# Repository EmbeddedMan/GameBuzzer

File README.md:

# GameBuzzer
Book club game buzzer project using LoRa Feathers

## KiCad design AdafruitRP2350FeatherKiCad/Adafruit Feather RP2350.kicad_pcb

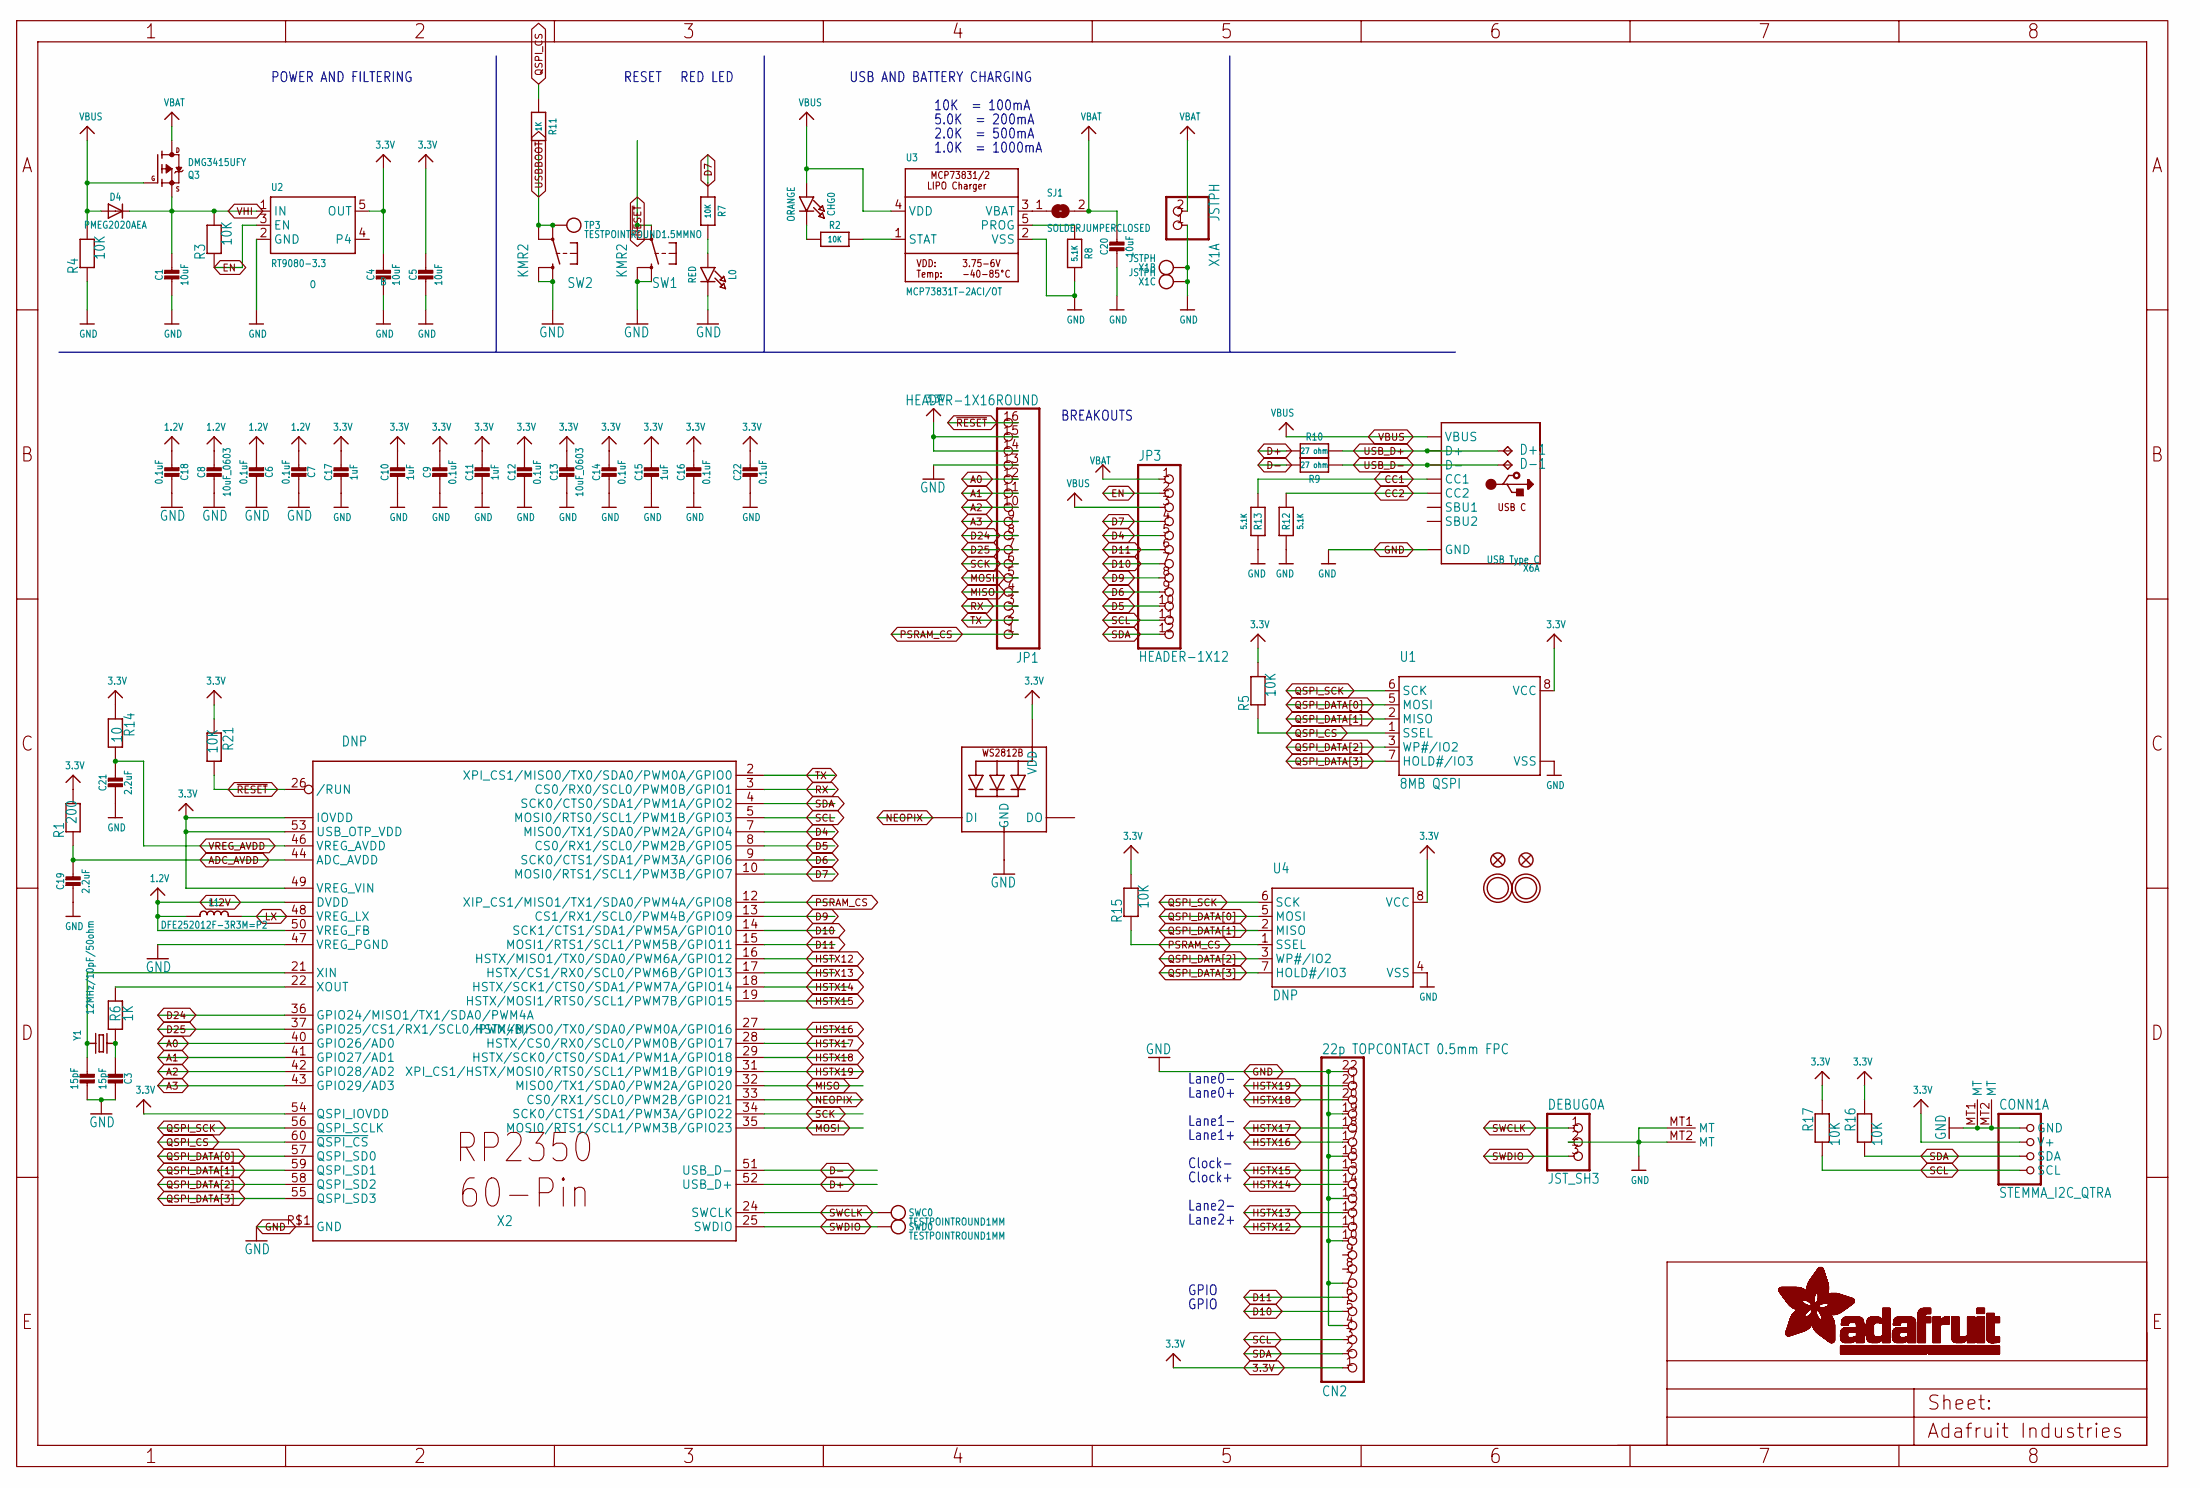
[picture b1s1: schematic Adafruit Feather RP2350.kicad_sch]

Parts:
C1, C4, C20: 10uF; 0805-NO
C2, C3: 15pF; _0402NO
C5: 10uF; 0603-NO
C6, C7, C9, C12, C14, C16, C18, C22: 0.1uF; _0402NO
C8, C13: 10uF_0603; _0603MP
C10, C11, C15, C17: 1uF; _0402NO
C19, C21: 2.2uF; _0402NO
CHG0: ORANGE; CHIPLED_0603_NOOUTLINE
CN2: 22p TOPCONTACT 0.5mm FPC; FPC_22PIN
CONN1: STEMMA_I2C_QTRA; JST_SH4_RA; LCSC C145961
D4: PMEG2020AEA; SOD-323F
D+1: TPB1,27; B1,27
D-1: TPB1,27; B1,27
DEBUG0: JST_SH3; JST_SH3_RA
JP1: HEADER-1X16ROUND; 1X16_ROUND
JP3: HEADER-1X12; 1X12_ROUND
L0: RED; CHIPLED_0603_NOOUTLINE
L1: DFE252012F-3R3M=P2; INDUCTOR_1007
LED1: WS2812B_SK6805_1515; SK6805_1515; LCSC C2890035
Q3: DMG3415UFY; DFN2015-3
R1: 200; _0402NO
R2, R3, R4, R5, R7, R15, R16, R17, R21: 10K; _0402NO
R6, R11: 1K; _0402NO
R8, R12, R13: 5.1K; _0402NO
R9, R10: 27 ohm; _0402NO
R14: 10; _0402NO
SJ1: SOLDERJUMPERCLOSED; SOLDERJUMPER_CLOSEDWIRE
SW1, SW2: KMR2; BTN_RKB2_4.6X2.8
SWC0: TESTPOINTROUND1MM; TESTPOINT_ROUND_1MM
SWD0: TESTPOINTROUND1MM; TESTPOINT_ROUND_1MM
TP3: TESTPOINTROUND1.5MMNO; TESTPOINT_ROUND_1.5MM_NO
U1: 8MB QSPI; USON8_4X4
U2: RT9080-3.3; SOT23-5; JLC_ROTATION 0
U3: MCP73831T-2ACI/OT; SOT23-5; JLC_ROTATION 0
U4: DNP; SOIC8_150MIL
U$31, U$32: MOUNTINGHOLE2.5; MOUNTINGHOLE_2.5_PLATED
U$34, U$35: FIDUCIAL_1MM
X1: JSTPH; JSTPH2_BATT; LCSC C47647
X2: DNP; QFN60_7MM_REDUCEDEPAD
X6: USB Type C; USB_C_CUSB31-CFM2AX-01-X; LCSC C165948
Y1: 12MHz/10pF/50ohm; CRYSTAL_2.5X2

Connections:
1.2V: C6.2, C7.2, C8.1, C18.2, L1.P$1 (1), X2.6 (DVDD), X2.23 (DVDD), X2.39 (DVDD), X2.50 (VREG_FB)
3.3V: C4.1, C5.1, C9.1, C10.1, C11.1, C12.1, C13.1, C14.1, C15.1, C16.1, C17.1, C22.1, CN2.1, CONN1.2 (V+), JP1.14, JP1.15, LED1.2 (VDD), R1.2, R5.2, R14.1, R15.2, R16.1, R17.1, R21.1, U1.8 (VCC), U2.5 (OUT), U4.8 (VCC), X2.1 (IOVDD), X2.11 (IOVDD), X2.20 (IOVDD), X2.30 (IOVDD), X2.38 (IOVDD), X2.45 (IOVDD), X2.49 (VREG_VIN), X2.53 (USB_OTP_VDD), X2.54 (QSPI_IOVDD)
A0: JP1.12, X2.40 (GPIO26/AD0)
A1: JP1.11, X2.41 (GPIO27/AD1)
A2: JP1.10, X2.42 (GPIO28/AD2)
A3: JP1.9, X2.43 (GPIO29/AD3)
ADC_AVDD: C19.1, R1.1, X2.44 (ADC_AVDD)
CC1: R13.2, X6.A5 (CC1)
CC2: R12.2, X6.B5 (CC2)
D4: JP3.5, X2.7 (MISO0/TX1/SDA0/PWM2A/GPIO4)
D5: JP3.10, X2.8 (CS0/RX1/SCL0/PWM2B/GPIO5)
D6: JP3.9, X2.9 (SCK0/CTS1/SDA1/PWM3A/GPIO6)
D7: JP3.4, R7.1, X2.10 (MOSI0/RTS1/SCL1/PWM3B/GPIO7)
D9: JP3.8, X2.13 (CS1/RX1/SCL0/PWM4B/GPIO9)
D10: CN2.5, JP3.7, X2.14 (SCK1/CTS1/SDA1/PWM5A/GPIO10)
D11: CN2.6, JP3.6, X2.15 (MOSI1/RTS1/SCL1/PWM5B/GPIO11)
D24: JP1.8, X2.36 (GPIO24/MISO1/TX1/SDA0/PWM4A)
D25: JP1.7, X2.37 (GPIO25/CS1/RX1/SCL0/PWM4B/)
D+: R10.2, X2.52 (USB_D+)
D-: R9.2, X2.51 (USB_D-)
EN: JP3.2, R3.1, U2.3 (EN)
GND: C1.2, C2.1, C3.1, C4.2, C5.2, C6.1, C7.1, C8.2, C9.2, C10.2, C11.2, C12.2, C13.2, C14.2, C15.2, C16.2, C17.2, C18.1, C19.2, C20.2, C21.2, C22.2, CN2.4, CN2.7, CN2.10, CN2.13, CN2.16, CN2.19, CN2.22, CONN1.1 (GND), CONN1.MT1 (MT), CONN1.MT2 (MT), DEBUG0.2, DEBUG0.MT1 (MT), DEBUG0.MT2 (MT), JP1.13, L0.C, LED1.4 (GND), R4.1, R8.2, R12.1, R13.1, SW1.B (S), SW1.B' (S1), SW2.B (S), SW2.B' (S1), U1.4 (VSS), U1.PAD (VSS), U2.2 (GND), U3.2 (VSS), U4.4 (VSS), X1.1, X1.NC1, X1.NC2, X2.47 (VREG_PGND), X2.P$1 (GND), X6.A1B12 (GND), X6.B1A12 (GND)
HSTX12: CN2.11, X2.16 (HSTX/MISO1/TX0/SDA0/PWM6A/GPIO12)
HSTX13: CN2.12, X2.17 (HSTX/CS1/RX0/SCL0/PWM6B/GPIO13)
HSTX14: CN2.14, X2.18 (HSTX/SCK1/CTS0/SDA1/PWM7A/GPIO14)
HSTX15: CN2.15, X2.19 (HSTX/MOSI1/RTS0/SCL1/PWM7B/GPIO15)
HSTX16: CN2.17, X2.27 (HSTX/MISO0/TX0/SDA0/PWM0A/GPIO16)
HSTX17: CN2.18, X2.28 (HSTX/CS0/RX0/SCL0/PWM0B/GPIO17)
HSTX18: CN2.20, X2.29 (HSTX/SCK0/CTS0/SDA1/PWM1A/GPIO18)
HSTX19: CN2.21, X2.31 (XPI_CS1/HSTX/MOSI0/RTS0/SCL1/PWM1B/GPIO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)
LX: L1.P$2 (2), X2.48 (VREG_LX)
MISO: JP1.4, X2.32 (MISO0/TX1/SDA0/PWM2A/GPIO20)
MOSI: JP1.5, X2.35 (MOSI0/RTS1/SCL1/PWM3B/GPIO23)
unnamed: CHG0.C, R2.1
unnamed: L0.A, R7.2
unnamed: R2.2, U3.1 (STAT)
unnamed: R8.1, U3.5 (PROG)
unnamed: C2.2, X2.21 (XIN), Y1.3 (2)
unnamed: C3.2, R6.1, Y1.1
unnamed: R6.2, X2.22 (XOUT)
unnamed: SJ1.1, U3.3 (VBAT)
NEOPIX: LED1.1 (DI), X2.33 (CS0/RX1/SCL0/PWM2B/GPIO21)
PSRAM_CS: JP1.1, R15.1, U4.1 (SSEL), X2.12 (XIP_CS1/MISO1/TX1/SDA0/PWM4A/GPIO8)
QSPI_CS: R5.1, R11.1, U1.1 (SSEL), X2.60 (~QSPI_CS)
QSPI_DATA[0]: U1.5 (MOSI), U4.5 (MOSI), X2.57 (QSPI_SD0)
QSPI_DATA[1]: U1.2 (MISO), U4.2 (MISO), X2.59 (QSPI_SD1)
QSPI_DATA[2]: U1.3 (WP#/IO2), U4.3 (WP#/IO2), X2.58 (QSPI_SD2)
QSPI_DATA[3]: U1.7 (HOLD#/IO3), U4.7 (HOLD#/IO3), X2.55 (QSPI_SD3)
QSPI_SCK: U1.6 (SCK), U4.6 (SCK), X2.56 (QSPI_SCLK)
RX: JP1.3, X2.3 (CS0/RX0/SCL0/PWM0B/GPIO1)
SCK: JP1.6, X2.34 (SCK0/CTS1/SDA1/PWM3A/GPIO22)
SCL: CN2.3, CONN1.4 (SCL), JP3.11, R17.2, X2.5 (MOSI0/RTS0/SCL1/PWM1B/GPIO3)
SDA: CN2.2, CONN1.3 (SDA), JP3.12, R16.2, X2.4 (SCK0/CTS0/SDA1/PWM1A/GPIO2)
SWCLK: DEBUG0.1, SWC0.P$1, X2.24 (SWCLK)
SWDIO: DEBUG0.3, SWD0.P$1, X2.25 (SWDIO)
TX: JP1.2, X2.2 (XPI_CS1/MISO0/TX0/SDA0/PWM0A/GPIO0)
USBBOOT: R11.2, SW2.A, SW2.A' (P1), TP3.P$1
USB_D+: D+1.TP, R10.1, X6.A6 (D+), X6.B6 (D+)
USB_D-: D-1.TP, R9.1, X6.A7 (D-), X6.B7 (D-)
VBAT: C20.1, JP3.1, Q3.3 (D), SJ1.2, X1.2
VBUS: CHG0.A, D4.A, JP3.3, Q3.1 (G), R4.2, U3.4 (VDD), X6.A4B9 (VBUS), X6.B4A9 (VBUS)
VHI: C1.1, D4.C, Q3.2 (S), R3.2, U2.1 (IN)
VREG_AVDD: C21.1, R14.2, X2.46 (VREG_AVDD)
~RESET: JP1.16, R21.2, SW1.A, SW1.A' (P1), X2.26 (/RUN)

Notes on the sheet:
RED LED
10K = 100mA
Lane0+
GPIO
Lane2+
Lane0-
1.0K = 1000mA
USB AND BATTERY CHARGING
Lane1-
Lane2-
Clock-
RESET
POWER AND FILTERING
2.0K = 500mA
Lane1+
BREAKOUTS
Clock+
5.0K = 200mA

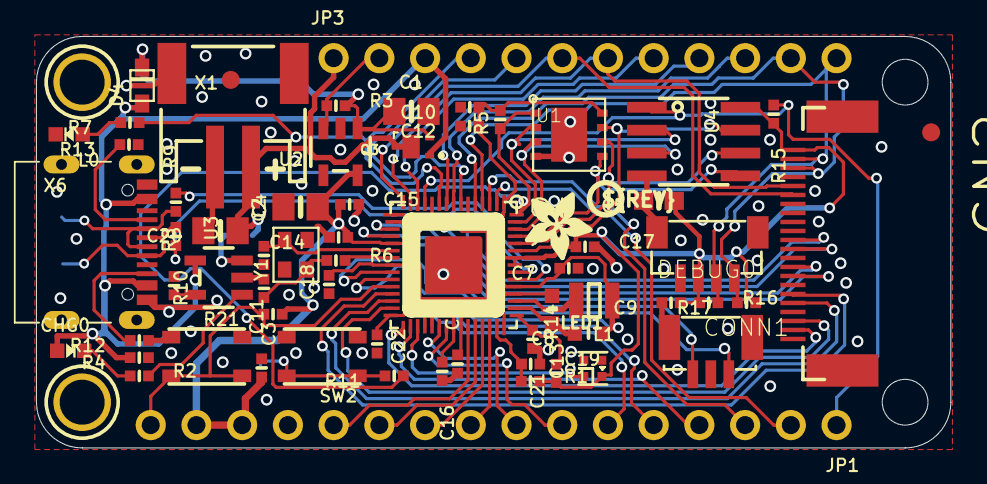
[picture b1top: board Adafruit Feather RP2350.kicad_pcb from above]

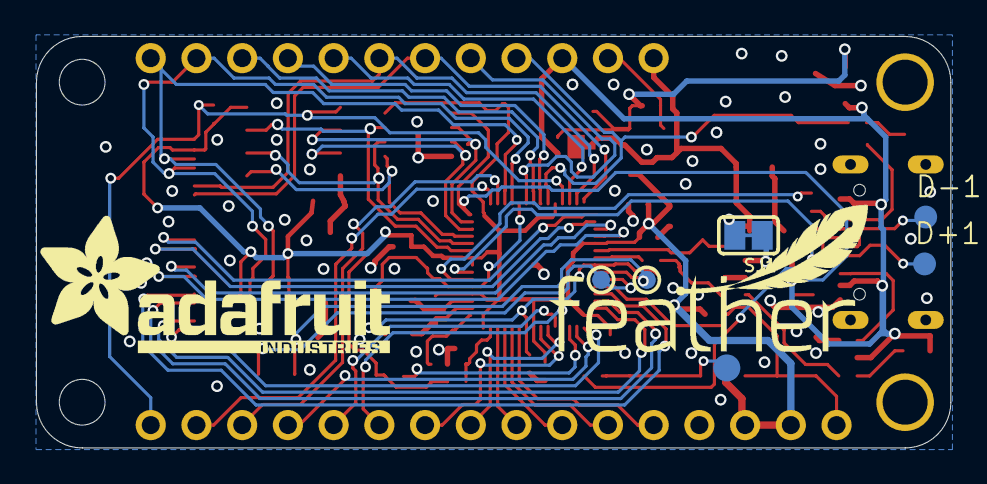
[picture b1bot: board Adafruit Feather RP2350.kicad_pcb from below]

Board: 2 copper layers, 50.8 x 22.9 mm, 145 parts (39 on the bottom side), 64 nets.

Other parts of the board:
PLABEL0: PLABEL0
PLABEL1: PLABEL1
PLABEL2: PLABEL2
PLABEL3: PLABEL3
PLABEL4: PLABEL4
PLABEL5: PLABEL5
PLABEL6: PLABEL6
PLABEL7: PLABEL7
PLABEL8: PLABEL8
PLABEL9: PLABEL9
PLABEL10: PLABEL10
PLABEL11: PLABEL11
PLABEL12: PLABEL12
PLABEL13: PLABEL13
PLABEL14: PLABEL14
PLABEL15: PLABEL15
PLABEL16: PLABEL16
PLABEL17: PLABEL17
PLABEL18: PLABEL18
PLABEL19: PLABEL19
PLABEL20: PLABEL20
PLABEL21: PLABEL21
PLABEL22: PLABEL22
PLABEL23: PLABEL23
PLABEL24: PLABEL24
PLABEL25: PLABEL25
PLABEL26: PLABEL26
PLABEL27: PLABEL27
PLABEL28: PLABEL28
PLABEL29: PLABEL29
PLABEL30: PLABEL30
PLABEL31: PLABEL31
PLABEL32: PLABEL32
PLABEL33: PLABEL33
PLABEL34: PLABEL34
PLABEL35: PLABEL35
PLABEL36: PLABEL36
PLABEL37: PLABEL37
PLABEL38: PLABEL38
PLABEL39: PLABEL39
PLABEL40: PLABEL40
PLABEL41: PLABEL41
PLABEL42: PLABEL42
PLABEL43: PLABEL43
PLABEL44: PLABEL44
PLABEL45: PLABEL45
PLABEL46: PLABEL46
PLABEL47: PLABEL47
PLABEL48: PLABEL48
PLABEL49: PLABEL49
PLABEL50: PLABEL50
PLABEL51: PLABEL51
PLABEL52: PLABEL52
PLABEL53: PLABEL53
PLABEL54: PLABEL54
PLABEL55: PLABEL55
PLABEL56: PLABEL56
PLABEL57: PLABEL57
PLABEL58: PLABEL58
PLABEL59: PLABEL59
PLABEL60: PLABEL60
PLABEL61: PLABEL61
PLABEL62: PLABEL62
PLABEL63: PLABEL63
PLABEL64: PLABEL64
PLABEL65: PLABEL65
PLABEL67: PLABEL67
PLABEL68: PLABEL68
U$73: ADAFRUIT_3.5MM
U$74: PCBFEAT-REV-040
U$75: FEATHERLOGO_MED
U$76: ADAFRUIT_TEXT_20MM
UNK_HOLE_0: dummyfp0
UNK_HOLE_1: dummyfp1

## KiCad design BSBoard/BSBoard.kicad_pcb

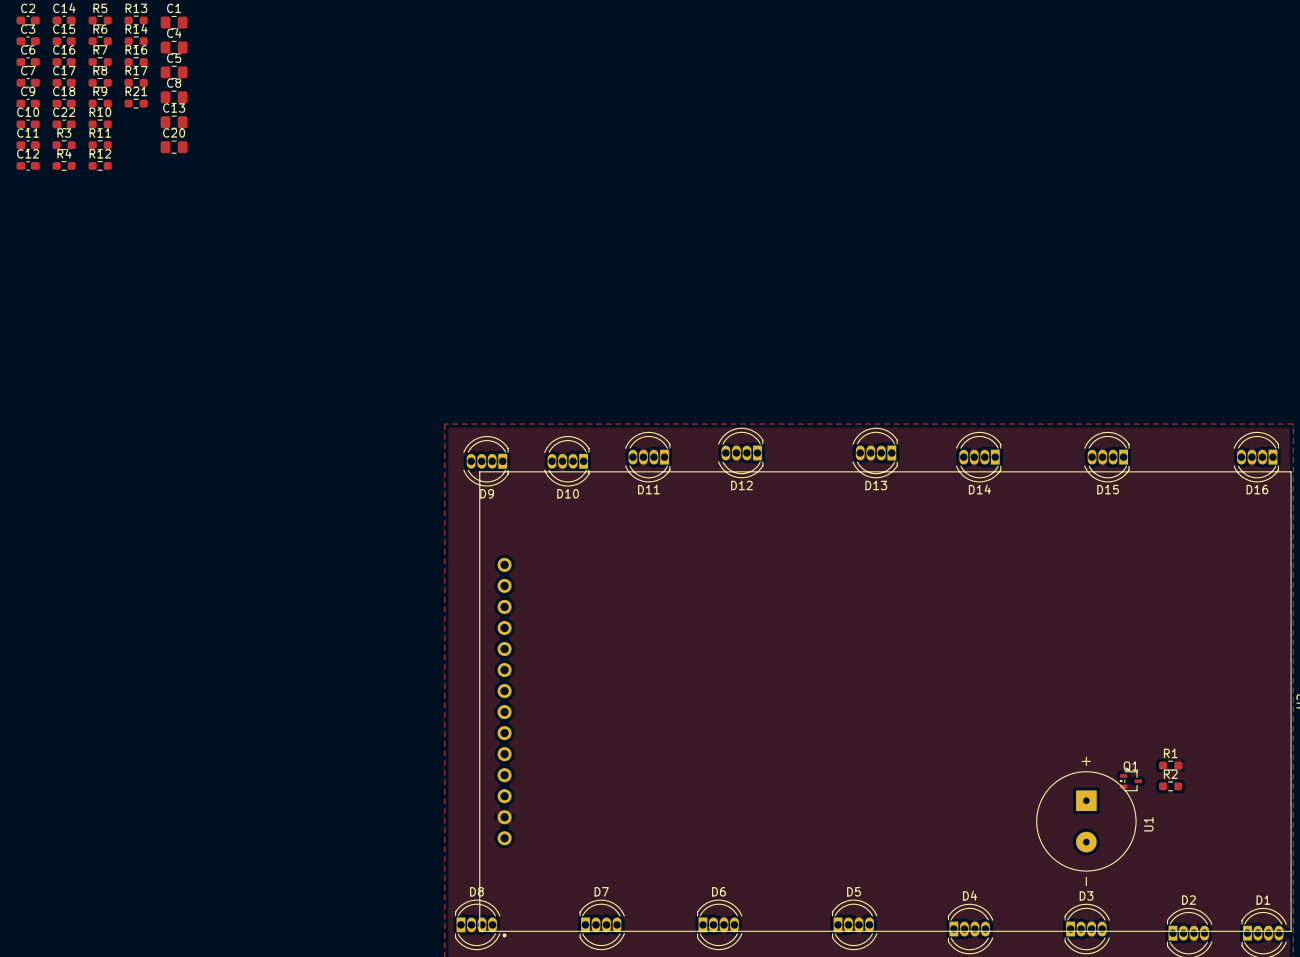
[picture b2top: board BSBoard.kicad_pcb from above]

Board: 2 copper layers, 56 parts (0 on the bottom side), 24 nets, no tracks yet.

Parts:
C1, C4, C5, C8, C13, C20: 10uF; C_0805_2012Metric_Pad1.18x1.45mm_HandSolder
C2, C3: 15pF; C_0603_1608Metric_Pad1.08x0.95mm_HandSolder
C6, C7, C9, C12, C14, C16, C18, C22: 0.1uF; C_0603_1608Metric_Pad1.08x0.95mm_HandSolder
C10, C11, C15, C17: 1uF; C_0603_1608Metric_Pad1.08x0.95mm_HandSolder
D1, D2, D3, D4, D5, D6, D7, D8, D9, D10, D11, D12, D13, D14, D15, D16: NeoPixel_THT; LED_D5.0mm-4_RGB
Q1: DMG1012T; SOT-323_SC-70
R1, R4, R5, R7, R8, R10, R21: 10K; R_0603_1608Metric_Pad0.98x0.95mm_HandSolder
R2: 220; R_0603_1608Metric_Pad0.98x0.95mm_HandSolder
R3: 200; R_0603_1608Metric_Pad0.98x0.95mm_HandSolder
R6, R11: 1K; R_0603_1608Metric_Pad0.98x0.95mm_HandSolder
R9, R12, R13: 5.1K; R_0603_1608Metric_Pad0.98x0.95mm_HandSolder
R14: 10; R_0603_1608Metric_Pad0.98x0.95mm_HandSolder
R16, R17: 27 ohm; R_0603_1608Metric_Pad0.98x0.95mm_HandSolder
U1: CMT-1209-590T; XDCR_CMT-1209-590T
U2: MSP3526; MSP3526_3.5in_LCD_Module_14Pin_P2.54mm

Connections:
1.2V: C6.2, C7.2, C8.1, C18.2
3.3V: C4.1, C5.1, C9.1, C10.1, C11.1, C12.1, C13.1, C14.1, C15.1, C16.1, C17.1, C22.1, R3.2, R10.2, R14.1, R21.1
+3V3: D1.2 (VDD), D2.2 (VDD), D3.2 (VDD), D4.2 (VDD), D5.2 (VDD), D6.2 (VDD), D7.2 (VDD), D8.2 (VDD), D9.2 (VDD), D10.2 (VDD), D11.2 (VDD), D12.2 (VDD), D13.2 (VDD), D14.2 (VDD), D15.2 (VDD), D16.2 (VDD), U1.P, U2.1 (VCC), U2.8 (LED)
GND: C1.2, C2.1, C3.1, C4.2, C5.2, C6.1, C7.1, C8.2, C9.2, C10.2, C11.2, C12.2, C13.2, C14.2, C15.2, C16.2, C17.2, C18.1, C20.2, C22.2, D1.3 (GND), D2.3 (GND), D3.3 (GND), D4.3 (GND), D5.3 (GND), D6.3 (GND), D10.3 (GND), D11.3 (GND), D12.3 (GND), D13.3 (GND), D14.3 (GND), D15.3 (GND), D16.3 (GND), Q1.2 (S), R1.2, R4.1, R9.2, R12.1, R13.1, U2.2 (GND)
unnamed: C3.2, R6.1
unnamed: D1.1 (DOUT), D2.4 (DIN)
unnamed: D2.1 (DOUT), D3.4 (DIN)
unnamed: D3.1 (DOUT), D4.4 (DIN)
unnamed: D4.1 (DOUT), D5.4 (DIN)
unnamed: D5.1 (DOUT), D6.4 (DIN)
unnamed: D6.1 (DOUT), D7.4 (DIN)
unnamed: D7.1 (DOUT), D8.4 (DIN)
unnamed: D8.1 (DOUT), D9.4 (DIN)
unnamed: D9.1 (DOUT), D10.4 (DIN)
unnamed: D10.1 (DOUT), D11.4 (DIN)
unnamed: D11.1 (DOUT), D12.4 (DIN)
unnamed: D12.1 (DOUT), D13.4 (DIN)
unnamed: D13.1 (DOUT), D14.4 (DIN)
unnamed: D14.1 (DOUT), D15.4 (DIN)
unnamed: D15.1 (DOUT), D16.4 (DIN)
unnamed: Q1.3 (D), U1.N
unnamed: Q1.1 (G), R1.1, R2.2
QSPI_CS: R10.1, R11.1
VHI: C1.1, R5.2

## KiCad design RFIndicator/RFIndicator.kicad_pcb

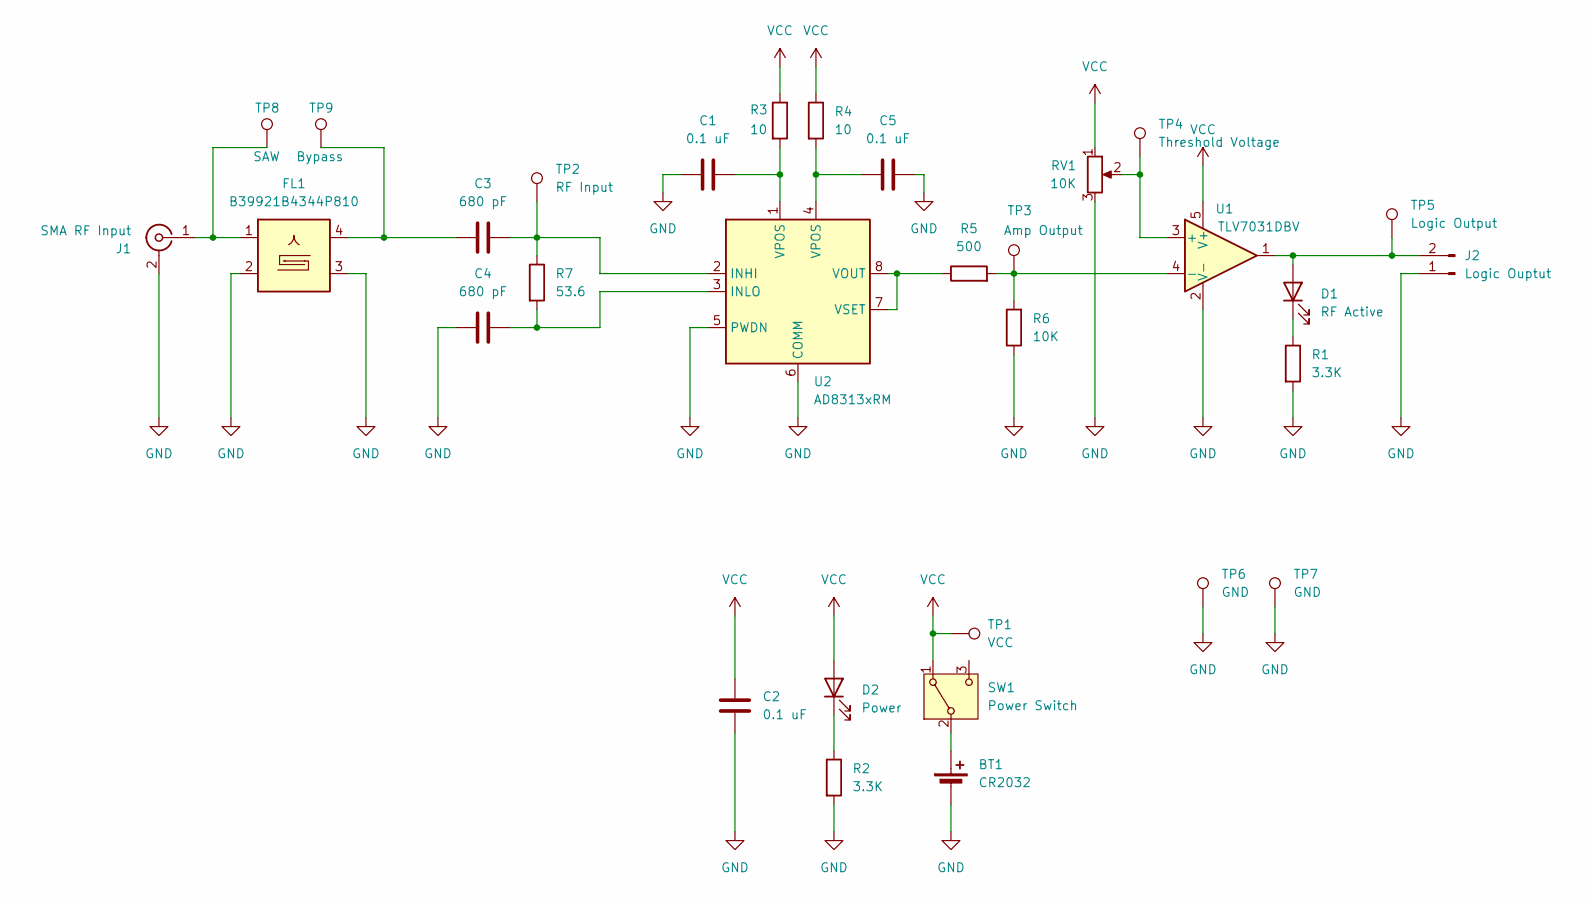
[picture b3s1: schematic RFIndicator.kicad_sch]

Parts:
BT1: CR2032; BatteryHolder_MYOUNG_BS-07-A1BJ001_CR2032
C1, C2, C5: 0.1 uF; C_0603_1608Metric_Pad1.08x0.95mm_HandSolder
C3, C4: 680 pF; C_0603_1608Metric_Pad1.08x0.95mm_HandSolder
D1: RF Active; LED_0603_1608Metric
D2: Power; LED_0603_1608Metric
FL1: B39921B4344P810; Filter_1411-5_1.4x1.1mm
J1: SMA RF Input; SMA_Samtec_SMA-J-P-H-ST-EM1_EdgeMount
J2: Logic Ouptut; PinHeader_1x02_P2.54mm_Vertical
R1, R2: 3.3K; R_0603_1608Metric_Pad0.98x0.95mm_HandSolder
R3, R4: 10; R_0603_1608Metric_Pad0.98x0.95mm_HandSolder
R5: 500; R_0603_1608Metric_Pad0.98x0.95mm_HandSolder
R6: 10K; R_0603_1608Metric_Pad0.98x0.95mm_HandSolder
R7: 53.6; R_0603_1608Metric_Pad0.98x0.95mm_HandSolder
RV1: 10K; Potentiometer_Bourns_3266W_Vertical
SW1: Power Switch; SW_SPDT_CK_JS102011SAQN
TP1: VCC; TestPoint_Loop_D2.54mm_Drill1.5mm_Beaded
TP2: RF Input; TestPoint_Loop_D2.54mm_Drill1.5mm_Beaded
TP3: Amp Output; TestPoint_Loop_D2.54mm_Drill1.5mm_Beaded
TP4: Threshold Voltage; TestPoint_Loop_D2.54mm_Drill1.5mm_Beaded
TP5: Logic Output; TestPoint_Loop_D2.54mm_Drill1.5mm_Beaded
TP6, TP7: GND; TestPoint_Loop_D2.54mm_Drill1.5mm_Beaded
TP8: SAW; TestPoint_Pad_1.0x1.0mm
TP9: Bypass; TestPoint_Pad_1.0x1.0mm
U1: TLV7031DBV; SOT-23-5
U2: AD8313xRM; MSOP-8_3x3mm_P0.65mm

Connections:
GND: BT1.2 (-), C1.1, C2.2, C4.1, C5.2, FL1.2, FL1.3, FL1.5, J1.2 (Ext), J2.1, R1.2, R2.2, R6.1, RV1.3, TP6.1, TP7.1, U1.2 (V-), U2.5 (PWDN), U2.6 (COMM)
unnamed: BT1.1 (+), SW1.2 (B)
unnamed: C1.2, R3.2, U2.1 (VPOS)
unnamed: C3.1, FL1.4, TP9.1
unnamed: C5.1, R4.2, U2.4 (VPOS)
unnamed: D1.2 (A), J2.2, TP5.1, U1.1
unnamed: D1.1 (K), R1.1
unnamed: D2.1 (K), R2.1
unnamed: FL1.1, J1.1 (In), TP8.1
unnamed: RV1.2, TP4.1, U1.3 (+)
unnamed: R5.2, R6.2, TP3.1, U1.4 (-)
unnamed: C3.2, R7.1, TP2.1, U2.2 (INHI)
unnamed: C4.2, R7.2, U2.3 (INLO)
unnamed: R5.1, U2.7 (VSET), U2.8 (VOUT)
VCC: C2.1, D2.2 (A), R3.1, R4.1, RV1.1, SW1.1 (A), TP1.1, U1.5 (V+)

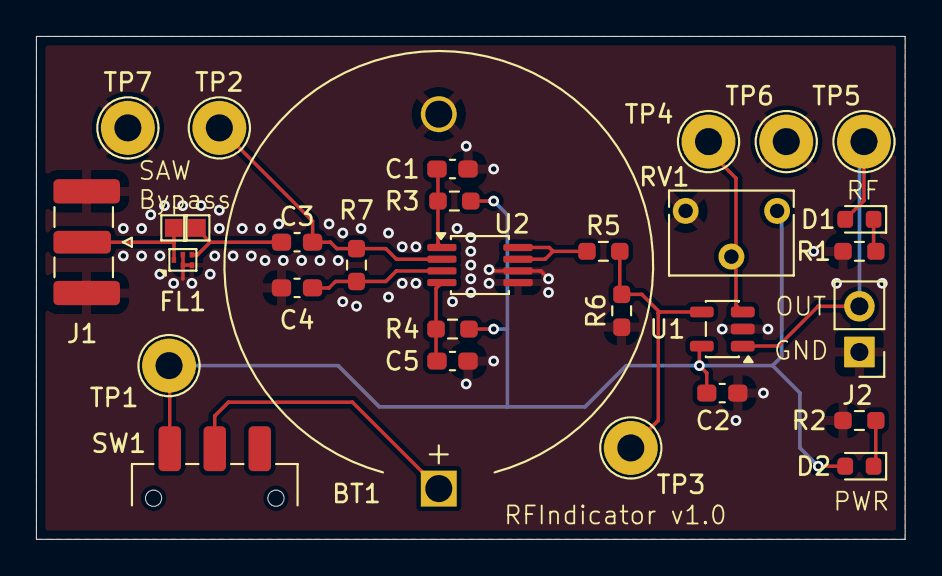
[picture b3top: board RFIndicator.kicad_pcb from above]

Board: 2 copper layers, 48.3 x 27.9 mm, 31 parts (0 on the bottom side), 15 nets.

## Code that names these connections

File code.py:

# SPDX-FileCopyrightText: 2023 Kattni Rembor for Adafruit Industries
# SPDX-License-Identifier: MIT

"""
CircuitPython Feather RP2040 RFM95 Packet Receive Demo

This demo waits for a "button" packet. When the first packet is received, the NeoPixel LED
lights up red. The next packet changes it to green. The next packet changes it to blue.
Subsequent button packets cycle through the same colors in the same order.

This example is meant to be paired with the Packet Send Demo code running
on a second Feather RP2040 RFM95 board.

board.A0 (GPIO26)
board.A1 (GPIO27)
board.A2 (GPIO28)
board.A3 (GPIO29)
board.BOOT board.BUTTON board.D7 (GPIO7)
board.D0 board.RX (GPIO1)
board.D1 board.TX (GPIO0)
board.D10 (GPIO10)
board.D11 (GPIO11)
board.D12 (GPIO12)
board.D13 board.LED (GPIO13)
board.D24 (GPIO24)
board.D25 (GPIO25)
board.D4 board.NEOPIXEL (GPIO4)
board.D5 (GPIO5)
board.D6 (GPIO6)
board.D9 (GPIO9)
board.MISO (GPIO8)
board.MOSI (GPIO15)
board.RFM_CS (GPIO16)
board.RFM_IO0 (GPIO21)
board.RFM_IO1 (GPIO22)
board.RFM_IO2 (GPIO23)
board.RFM_IO3 (GPIO19)
board.RFM_IO4 (GPIO20)
board.RFM_IO5 (GPIO18)
board.RFM_RST (GPIO17)
board.SCK (GPIO14)
board.SCL (GPIO3)
board.SDA (GPIO2)

"""

import board
import digitalio
import neopixel
import adafruit_rfm9x
import time

# LED setup (for heartbeat)
led = digitalio.DigitalInOut(board.LED)
led.direction = digitalio.Direction.OUTPUT

# Set up NeoPixel.
pixel = neopixel.NeoPixel(board.NEOPIXEL, 1)
pixel.brightness = 0.5

# Define the possible NeoPixel colors.
color_values = [
    (255, 0, 0),
    (0, 255, 0),
    (0, 0, 255),
]
COLOR_RED = 0
COLOR_GREEN = 1
COLOR_BLUE = 2

# Define radio frequency in MHz. Must match your
# module. Can be a value like 915.0, 433.0, etc.
RADIO_FREQ_MHZ = 915.0

# Define Chip Select and Reset pins for the radio module.
CS = digitalio.DigitalInOut(board.RFM_CS)
RESET = digitalio.DigitalInOut(board.RFM_RST)

# Initialise RFM95 radio
rfm95 = adafruit_rfm9x.RFM9x(board.SPI(), CS, RESET, RADIO_FREQ_MHZ)

# Set up the onboard button
btn = digitalio.DigitalInOut(board.BUTTON)
btn.direction = digitalio.Direction.INPUT
btn.pull = digitalio.Pull.UP

###################
#  BASE STATION   #
###################

# All packets sent between any nodes will consist of the folowing:
# Each packet will consist of four bytes.
# Packet Structure:
#   Byte 1: Source address (0 = base station, 1 - 8 = hand controllers)
#   Byte 2: Destination address (0 = base station, 1 - 8 = hand controllers)
#   Byte 3: Status byte
#   Byte 4: Battery voltage (0 = 0.0v, 255 = 4.7v)
#
# Status byte for hand controller -> base station
# 0 = Heartbeat only. Button not pushed.
# 1 = Button has been pushed.
#
# Status byte for base station -> hand controller (ACK packets)
# 0 = Turn your LED to green (system reset)
# 1 = Turn your LED to red (your button press has been recorded)
#
# Battery voltage byte will always be 0 in packets sent from base station.
# Heartbeats will be sent from hand controller to base station every 1s.
# When a hand controller button push happens, the hand controller will
#   immediately send a packet with status = 1 to the base station.
# When the hand controller button is released, a heartbeat packet is
#   immediately sent.
# Every packet received at the base station must be acknowledged by an ACK
#   packet.
# The ACK packet has the base station's address (0) as the first byte.
# The ACK packet has the destination hand controller's address (1-8) as the
#   second byte.
# The base station has a screen. This screen displays the current
#   state of every hand controller (pressed/unpressed/no comms) in real
#   time as well as the controller's battery level.
# The base station has a 'Reset' button. When this button is pressed,
#   the base station resets the display and begins watching for the first
#   button push from each hand controller and records the order in which
#   their buttons were pushed.
# When in the 'reset' state (waiting for first controller's button push)
#   the base station will ack with a status byte value of 0 which will make
#   all of the hand controler's neopixels green, indicating that the system
#   is waiting for the first person to press their button.
# Once the base station receives the first button push message from a
#   hand controller, it will begin acking that hand controller with a status
#   byte value of 1 which will make the hand controller's neopixel turn red,
#   indicating that the button push has been registered at the base station.
# After reset, the base station will display its neopixel as green. Once it
#   receives the first button press it will display as red.

# Define the two types of ack packets the base station will send to the hand controllers
ack_green_pkt = bytes([0, 0, 0, 0])
ack_red_pkt = bytes([0, 0, 1, 0])

# Keep track of what 'mode' we are in
base_station_is_reset = True

# Stores the time at which we reset and started waiting for button press packets
# And we start each boot being in reset mode
reset_start_time = time.monotonic()

# Stores the absolute time of reception of the first button push packet from
# each hand controller. 0.0 means the base station has not received a button
# push packet since the last reset.
button_push_time = [0.0, 0.0, 0.0, 0.0, 0.0, 0.0, 0.0, 0.0]


# Wait to receive packets.
print("Reset: waiting for hand controllers to press buttons")
# Start off with our LED showing green
pixel.fill(color_values[COLOR_GREEN])

while True:
    # Toggle the red LED on the board
    led.value = not led.value

    # Look for button press to reset our state
    if not btn.value:
        base_station_is_reset = True
        button_push_time = [0.0, 0.0, 0.0, 0.0, 0.0, 0.0, 0.0, 0.0]
        pixel.fill(color_values[COLOR_GREEN])
        print("System now reset")

    # Look for a new packet - wait up to 0.25 second:
    packet = rfm95.receive(timeout=0.25)
    # If no packet was received during the timeout then None is returned.
    if packet is not None:
        # Check the packet length
        if len(packet) == 4:
            hc_src_addr = int.from_bytes(packet[0:1], "big")
            hc_dst_addr = int.from_bytes(packet[1:2], "big")
            hc_status = int.from_bytes(packet[2:3], "big")
            hc_battery = int.from_bytes(packet[3:4], "big")
            if hc_src_addr != 0 and hc_src_addr <= 8:
                if hc_dst_addr == 0:
                    if hc_status == 0:  # heartbeat packet
                        if button_push_time[hc_src_addr] == 0.0:
                            rfm95.send(bytes([0, hc_src_addr, 0, 0]))
                        else:
                            rfm95.send(bytes([0, hc_src_addr, 1, 0]))
                    else:
                        if hc_status == 1:  # button push packet
                            if button_push_time[hc_src_addr] == 0.0:
                                print("Got button push from hand controller ", hc_src_addr)
                                button_push_time[hc_src_addr] = time.monotonic();
                            pixel.fill(color_values[COLOR_RED])
                            rfm95.send(bytes([0, hc_src_addr, 1, 0]))
                        else:
                            print("Got an unknown status byte")
                else:
                    print("Got a packet with a bad destination address of ", hc_dst_addr)
            else:
                print("Got a packet with a bad source address of ", hc_src_addr)
        else:
            print("Packet recevied with bad length of ", len(packet))

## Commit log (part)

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2025-11-07 First check in. Python versions of Hand Controller and Base Station are working and have been used at 2 book clubs. C (Arduino) version of Hand Controller is done being ported. C (Arduino) version of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
2025-11-08 Colors now correct, correct display driver used.
2025-11-08 Fixed compile error
2025-11-11 Bringing the C closer to the Python for the base station
2025-11-11 Forgot to check these in
2025-11-13 C version of both hand controller and base station now working. Not 100% (no sorted order output on screen yet), but all basic communications is there, and at 200ms cycle time.
2025-11-14 Maxed out (actually too fast - out of spec for display) SPI speed when writing to display at 62.5MHz.
2025-11-16 Mostly working, but sorting and serial.print are problems
2025-11-28 Finally found and fixed random USB serial print bug : RF95 transmit causes power drop below RP2040 USB threshold which kills USB PHY. Solution: limit RF95 transmit power. (10 appears to work)
2025-11-29 RFIndicator PCB project check in. Sent rev 1.0 boards to JLC for fab today.
2025-11-30 Created BOM, ordered from DigiKey. Holy crap I picked the wrong RF Log Amp. $32 ea! I could have used a lot cheaper one.
2026-01-09 Got tons of stuff working - RFM SPI is much faster, solid RF performance (I think). Have not started doing GUI updates yet.
2026-01-10 Got PNG rendering working with TFT_eSPI graphics library, but can't get it to work on same SPI bus as radio.
2026-01-10 Final version before tonight's book club.
2026-01-11 Can't display BMPs.
2026-01-11 Set up hand controllers to attempt to keep time even if base station time sync packet is missing. Tested by having base station skip every 10th packet. RF analyzer shows it appears to work.
